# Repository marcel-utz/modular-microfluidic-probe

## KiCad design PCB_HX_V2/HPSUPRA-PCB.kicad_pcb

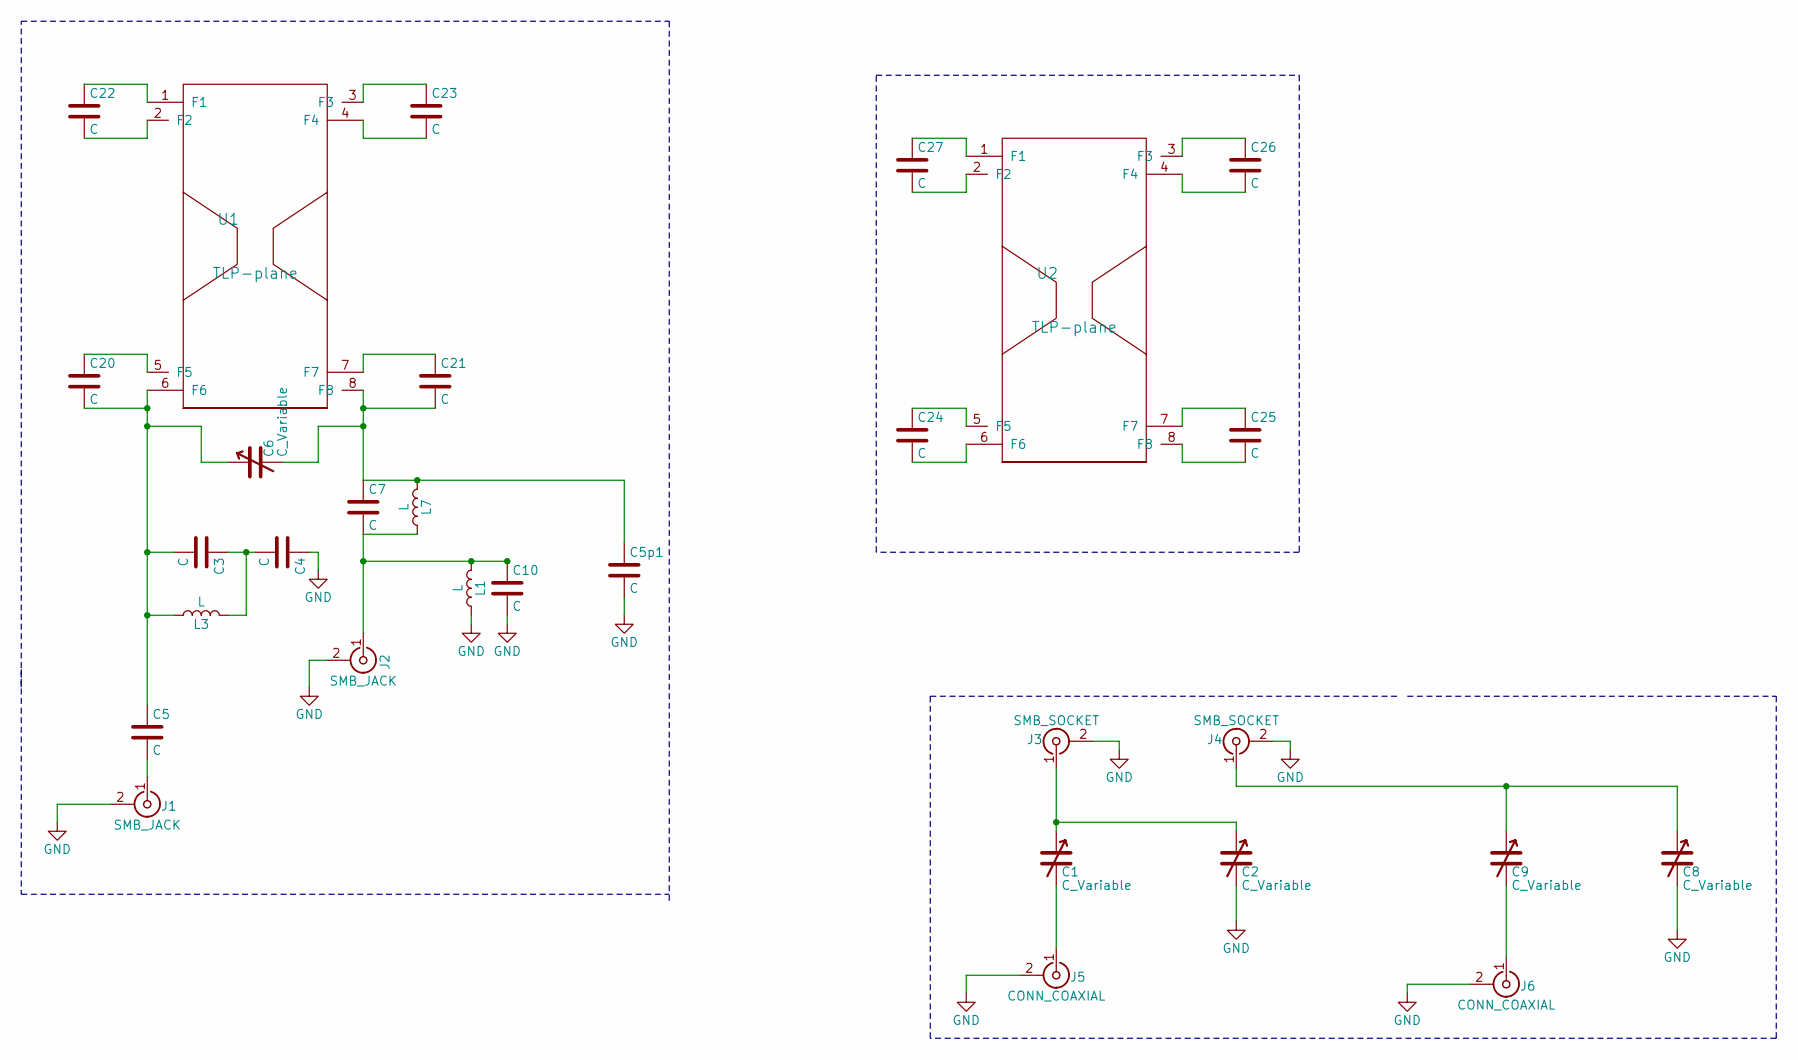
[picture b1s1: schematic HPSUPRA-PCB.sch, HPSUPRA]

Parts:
C1, C2, C8, C9: C_Variable; NMAT_25HV
C3, C4, C5, C5p1, C7, C10, C20, C21, C22, C23, C24, C25, C26, C27: C; C_1210_HandSoldering
C6: C_Variable; VOLTRONICS_NMAJ25HV
J1, J2: SMB_JACK; SMP_RA
J3, J4: SMB_SOCKET; SMA_TH
J5, J6: CONN_COAXIAL; RG402_TRHU
L1: L; IND_COILCRAFT_1212VS
L3, L7: L; IND_908SQ-17N
U1, U2: TLP-plane; TLP_75x25_7x1.5_v1

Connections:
GND: C2.2, C4.1, C5p1.2, C8.2, C10.2, J1.2 (Ext), J2.2 (Ext), J3.2 (Ext), J4.2 (Ext), J5.2 (Ext), J6.2 (Ext), L1.1; also elsewhere on the board
unnamed: C1.1, C2.1, J3.1 (In)
unnamed: C3.1, C4.2, L3.2
unnamed: C5.2, J1.1 (In)
unnamed: C8.1, C9.1, J4.1 (In)
unnamed: C7.2, C10.1, J2.1 (In), L1.2, L7.1
unnamed: C20.1, U1.5 (F5)
unnamed: C3.2, C5.1, C6.1, C20.2, L3.1, U1.6 (F6)
unnamed: C21.1, U1.7 (F7)
unnamed: C5p1.1, C6.2, C7.1, C21.2, L7.2, U1.8 (F8)
unnamed: C22.1, U1.1 (F1)
unnamed: C22.2, U1.2 (F2)
unnamed: C23.1, U1.3 (F3)
unnamed: C23.2, U1.4 (F4)
unnamed: C24.1, U2.5 (F5)
unnamed: C24.2, U2.6 (F6)
unnamed: C25.1, U2.7 (F7)
unnamed: C25.2, U2.8 (F8)
unnamed: C26.1, U2.3 (F3)
unnamed: C26.2, U2.4 (F4)
unnamed: C27.1, U2.1 (F1)
unnamed: C27.2, U2.2 (F2)
unnamed: C1.2, J5.1 (In)
unnamed: C9.2, J6.1 (In)

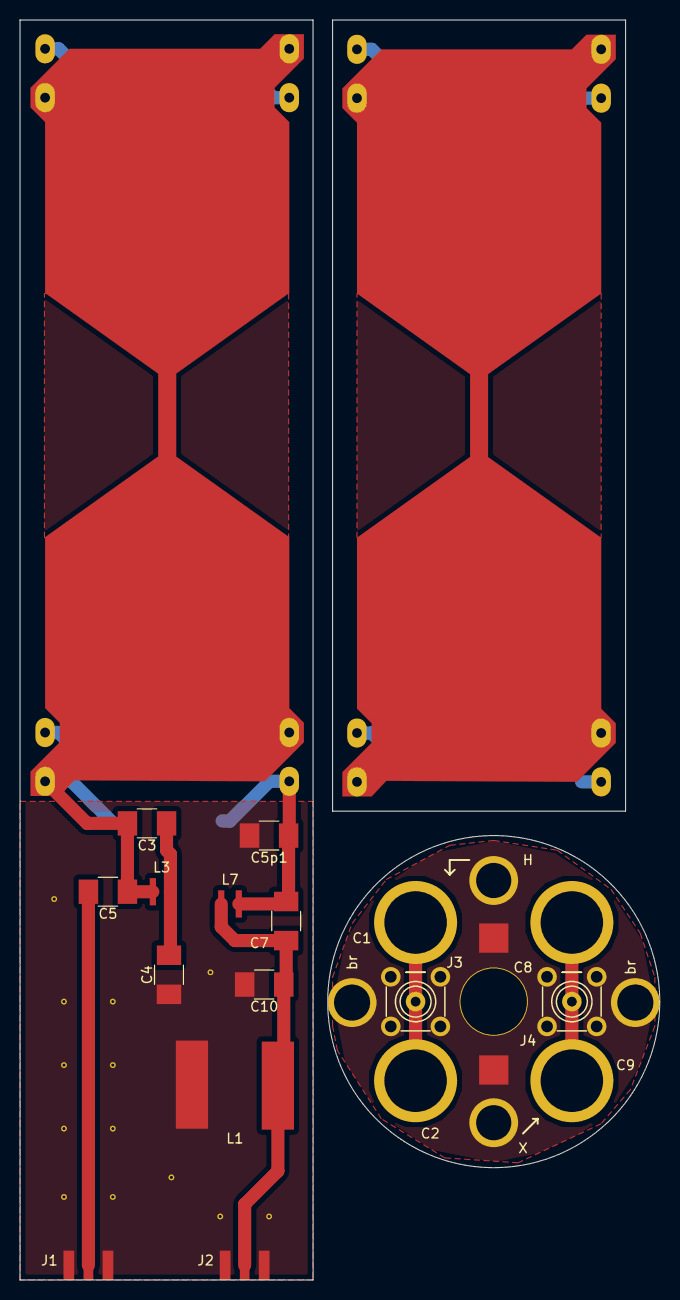
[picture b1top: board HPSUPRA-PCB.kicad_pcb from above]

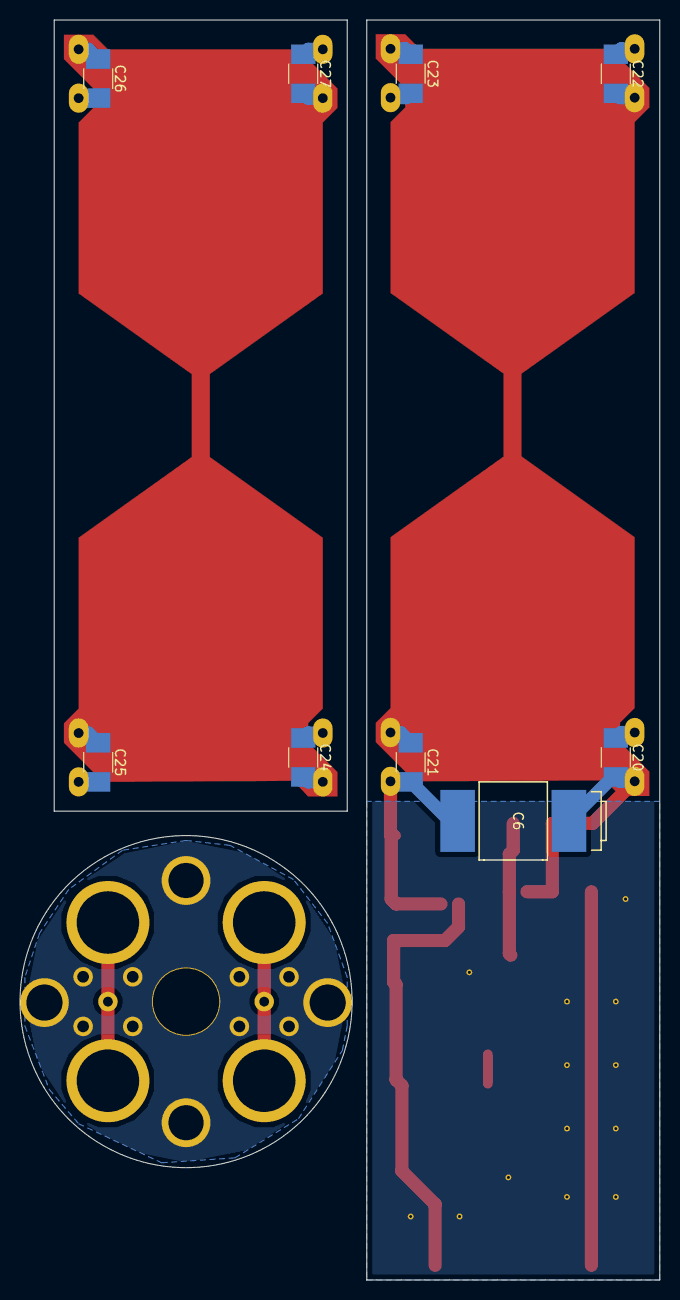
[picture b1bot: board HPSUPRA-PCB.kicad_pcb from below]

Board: 2 copper layers, 65.5 x 129.0 mm, 32 parts (9 on the bottom side), 22 nets.

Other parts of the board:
H: CONN_COAXIAL; RG402_TRHU
X: CONN_COAXIAL; RG402_TRHU
br: CONN_COAXIAL; RG402_TRHU
br#2: CONN_COAXIAL; RG402_TRHU

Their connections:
GND: H.2, X.2, br.2, br#2.2; also elsewhere on the board

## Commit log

2019-02-05 Adding probe and PCB designs
